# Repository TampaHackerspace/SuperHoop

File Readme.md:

#Orlando Mini Maker Faire Project Planner
#Super Hoop

##Objective
Create a spectacle to attract attention and bring people into our exhibit so that our members can talk about their projects and we can promote our new Tampa Hackerspace. The project should be portable and kid friendly for future use.

##Project Idea
Embed addressable LEDs into clear hula hoops and instrument them with a programmable microcontroller and sensors so that we can make games and use them creatively.

##Sensors
accelerometer
photo electric cell and/or color sensor
grip sensor
proximity sensors

##Applications / Games
Persistence of Vision display. Spin the hoops rapidly to make colorful displays

How high can you go? Compete to see who can toss the hoop the highest and safely catch it.

Ring toss. Two or more players toss the hoops between themselves. Take a step back at each successful catch and keep going to see how long you can keep the game going.

Ultimate Ring Golf: Play it like ultimate frisbee but use the rings.

Horseshoes: Rings instead of horseshoes. Same rules.

Fasted hoop: First one to spin their hoop hula style 100 rotations wins.

Billboard: Use a wireless controller to stream dynamic text that displays while spinning?

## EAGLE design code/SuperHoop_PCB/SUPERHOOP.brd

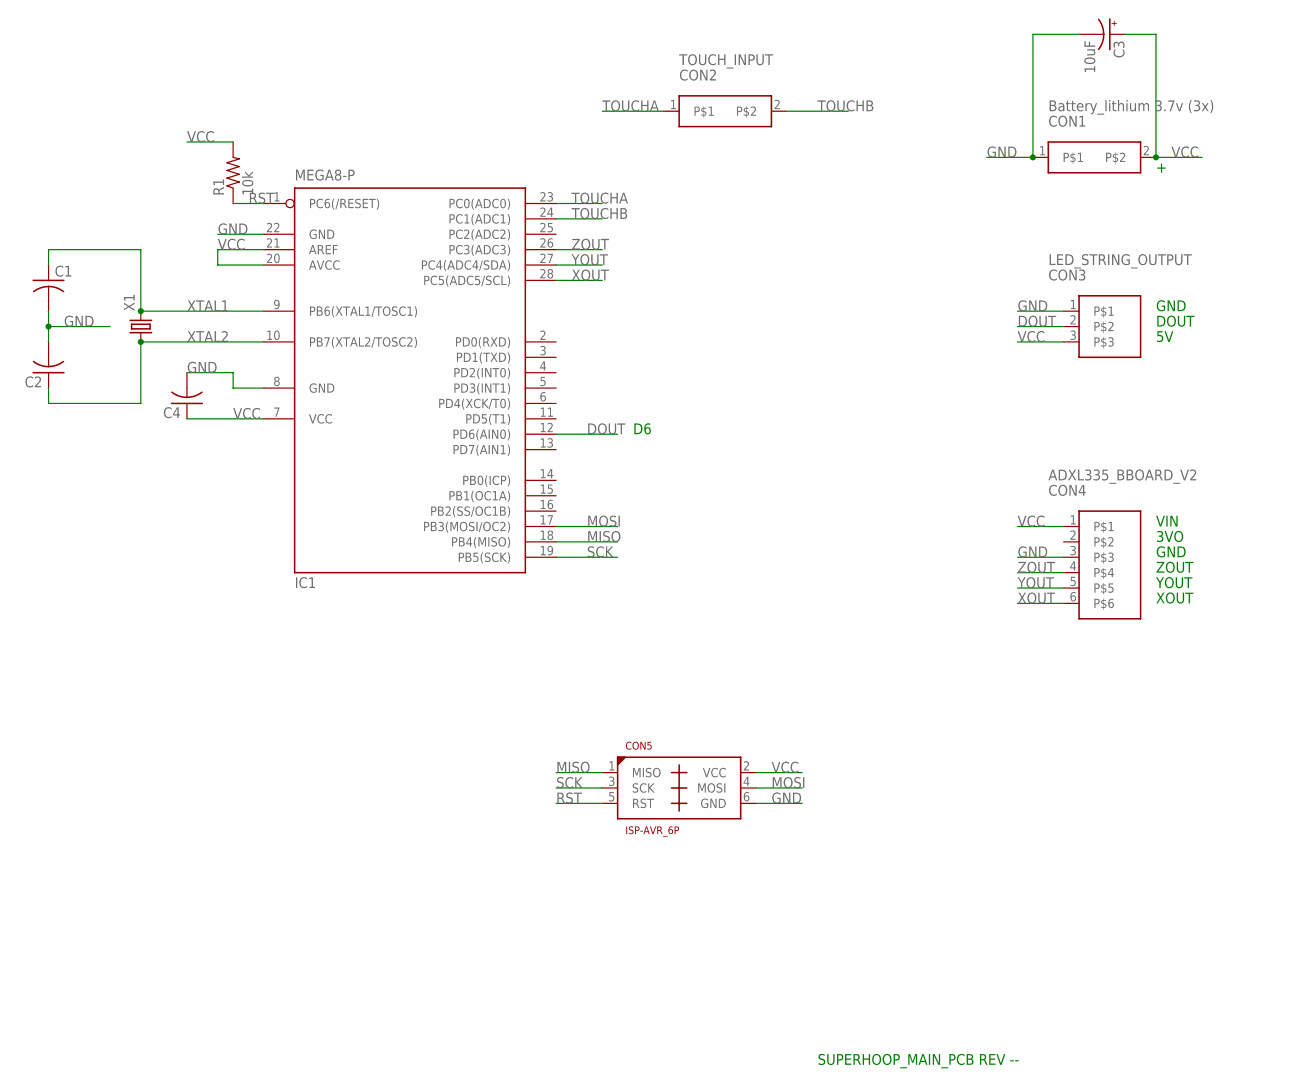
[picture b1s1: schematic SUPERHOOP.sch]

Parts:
C1, C2, C4: C-US025-024X044; C025-024X044
C3: 10uF; E2,5-5
CON1: Battery_lithium 3.7v (3x); HEADER_2X1_2.54
CON2: TOUCH_INPUT; HEADER_2X1_2.54
CON3: LED_STRING_OUTPUT; HEADER_3X1_2.54
CON4: ADXL335_BBOARD_V2; HEADER_6X1_2.54
CON5: ISP-AVR_6P; HEADER_3X2_2.54
IC1: MEGA8-P; DIL28-3
R1: 10k; 0207/12
X1: CRYSTALHC49S; HC49/S

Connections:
DOUT: CON3.2, IC1.12 (PD6(AIN0))
GND: C1.2, C2.2, C3.-, C4.2, CON1.1, CON3.1, CON4.3, CON5.6 (GND), IC1.8 (GND), IC1.22 (GND)
MISO: CON5.1 (MISO), IC1.18 (PB4(MISO))
MOSI: CON5.4 (MOSI), IC1.17 (PB3(MOSI/OC2))
RST: CON5.5 (RST), IC1.1 (PC6(/RESET)), R1.1
SCK: CON5.3 (SCK), IC1.19 (PB5(SCK))
TOUCHA: CON2.1, IC1.23 (PC0(ADC0))
TOUCHB: CON2.2, IC1.24 (PC1(ADC1))
VCC: C3.+, C4.1, CON1.2, CON3.3, CON4.1, CON5.2 (VCC), IC1.7 (VCC), IC1.20 (AVCC), IC1.21 (AREF), R1.2
XOUT: CON4.6, IC1.28 (PC5(ADC5/SCL))
XTAL1: C1.1, IC1.9 (PB6(XTAL1/TOSC1)), X1.2
XTAL2: C2.1, IC1.10 (PB7(XTAL2/TOSC2)), X1.1
YOUT: CON4.5, IC1.27 (PC4(ADC4/SDA))
ZOUT: CON4.4, IC1.26 (PC3(ADC3))

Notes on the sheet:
GND
DOUT
VIN
ZOUT
YOUT
XOUT
3VO
SUPERHOOP_MAIN_PCB REV --

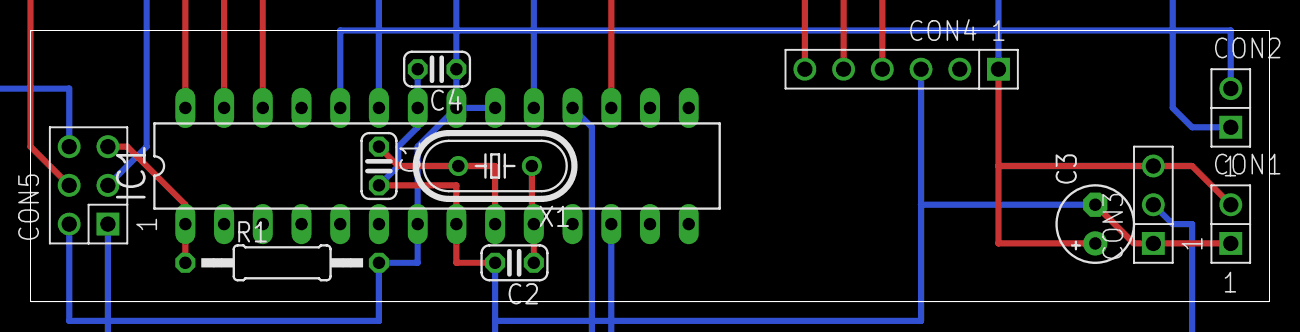
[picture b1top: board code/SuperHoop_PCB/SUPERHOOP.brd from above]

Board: 2 copper layers, 81.3 x 17.8 mm, 12 parts (0 on the bottom side), 14 nets.

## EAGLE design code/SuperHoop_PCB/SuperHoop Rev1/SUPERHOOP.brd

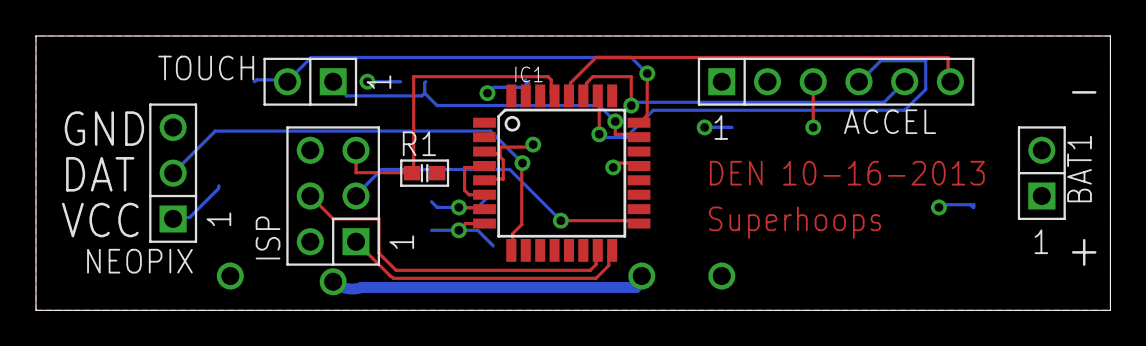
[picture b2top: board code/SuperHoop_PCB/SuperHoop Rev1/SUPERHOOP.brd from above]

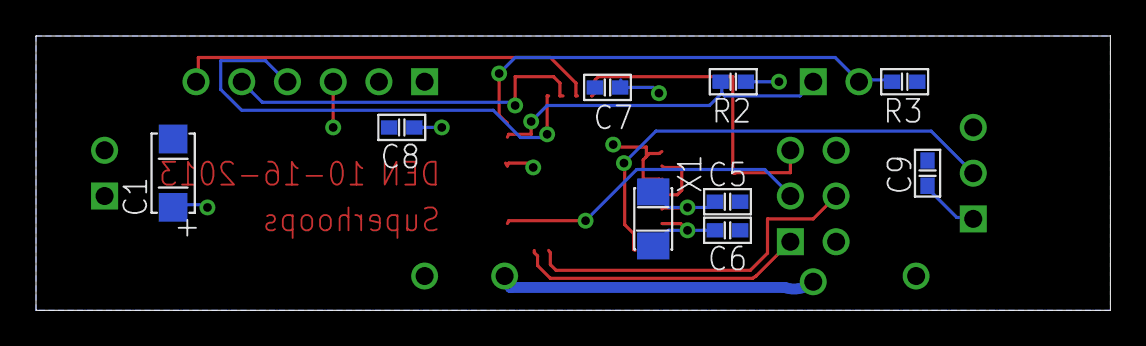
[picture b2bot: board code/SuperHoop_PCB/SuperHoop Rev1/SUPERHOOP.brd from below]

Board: 2 copper layers, 59.7 x 15.2 mm, 16 parts (9 on the bottom side), 14 nets.

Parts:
ACCEL: ADXL335_BBOARD_V2; HEADER_6X1_2.54
BAT1: Battery_lithium 3.7v (3x); HEADER_2X1_2.54
C1: 10uF; CAP_POL_1206
C5, C6: 22pF; SMD_0603
C7, C9: 100nF; SMD_0603
C8: 100nf; SMD_0603
IC1: MEGA8-AI; TQFP32-08
ISP: ISP-AVR_6P; HEADER_3X2_2.54
NEOPIX: LED_STRING_OUTPUT; HEADER_3X1_2.54
R1: 10k; SMD_0603
R2, R3: 460k; SMD_0603
TOUCH: TOUCH_INPUT; HEADER_2X1_2.54
X1: 16mhz; CRYSTAL_3.2X1.5

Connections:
DOUT: IC1.9, NEOPIX.2
GND: ACCEL.3, BAT1.2, C1.N, C5.P$1, C6.P$2, C7.P$2, C8.P$1, C9.P$2, IC1.3, IC1.5, IC1.21, ISP.6, NEOPIX.3, R3.P$1
MISO: IC1.16, ISP.1
MOSI: IC1.15, ISP.4
RST: IC1.29, ISP.5, R1.P$1
SCK: IC1.17, ISP.3
TOUCHA: IC1.23, R2.P$1, TOUCH.1
TOUCHB: IC1.24, R3.P$2, TOUCH.2
VCC: ACCEL.1, BAT1.1, C1.P, C7.P$1, C8.P$2, C9.P$1, IC1.4, IC1.6, IC1.18, IC1.20, ISP.2, NEOPIX.1, R1.P$2, R2.P$2
XOUT: ACCEL.6, IC1.28
XTAL1: C5.P$2, IC1.7, X1.P$1
XTAL2: C6.P$1, IC1.8, X1.P$2
YOUT: ACCEL.5, IC1.27
ZOUT: ACCEL.4, IC1.26

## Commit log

2013-09-22 Add comments to the replaceColor function
2013-09-22 Added SuperHoopStrandtet folder so arduino env doesnt whine
2013-09-22 Added ADXL335 testing code
2013-09-22 Added in accelerometer integration test so that the frame it is rendering is dependent on the angle
2013-09-22 Changed drawpixels to render_frame to allow rendering arbitrary frames out of order
2013-09-22 added list of parts needed to buy
2013-09-22 Adding a second array with a larger 18x18 pattern
2013-09-22 updating replaceColor routine to switch case so I can fully light an LED wit 8 bit value
2013-09-22 Adding a bitmap pattern for use in conversion
2013-09-22 Fixed some missing curly braces
2013-09-22 Lie detector code for arduino
2013-09-22 Added a second pattern
2013-09-22 Updated parts needed with sources
2013-09-23 Created bitmap2hoop to generate patterns, requries 18x18 pattern
2013-09-23 Changed bitmap2hoop to support arbitrary sized images
2013-09-25 Added LV per request from Tabatha
2013-09-25 patterns for superhoop
2013-09-25 Supplemented the initial pattern with Tabatha's LV pattern
    updated to 18x18 pattern matrix, changed patterns
2013-09-26 Add script to generate patterns from the Patterns directory using the Java app. Generated all patterns
2013-09-26 Added in test code for selecting patterns
2013-09-27 Updated converter to take multiple files
2013-09-28 Updated to multi-pattern output
    Sum ting wong, the repeat pattern appears to crash the Arduino
2013-09-28 Working without pointers
    Working version that doesn't use pointers. cycles through our 9 current
    patterns every 20-ish seconds
2013-09-28 Removed serial routines
2013-09-28 reversed some whites
    more visible, less overpowering with less white backgrounds
2013-09-29 Added Eagle Schematic
2013-09-29 PCB layout complete
2013-09-29 Added Adafruit Neopixel library
2013-09-29 lie detector changes
2013-09-30 final changes from Sunday
    Saved Eagle files, shortened delay between pattern cycles to ~5 seconds
2013-09-30 compilable code
2013-10-01 Create Toss-Up
    See how high you can toss the hoop. Light show after the toss measures how high it went.
2013-10-01 commit
    Made a project folder for Toss-Up
2013-10-01 Added BMPs for all patterns and the bitmask output
2013-10-02 Added thumbsdb
2013-10-02 integrated lie detector
2013-10-02 created PDF of schematic
2013-10-02 circuit board closeup pics for troubleshooting
2013-10-02 Fixed wrong wiring
    made the board wiring more readable
2013-10-03 Fixed some wiring glitches
    missing reset pin and removed layer covering wires under crystal
2013-10-04 4 Pattern Demo for Orlando
2013-10-05 Converted patterns to const
2013-10-17 pcb for production
    moved to SMD comps and laid out for production
2013-10-17 Revised BOM
    Added 2 layer prints and added BOM to schematic
2013-10-17 flipped right side up
    Schematic printer backwards, corrected this so it's readable.
2013-10-27 Gerbers as sent to Oshpark
2013-10-27 Fixed crystal footprint
    rev1 had 3.2x1.5, should have been 5.0x3.2 to fit specified part
